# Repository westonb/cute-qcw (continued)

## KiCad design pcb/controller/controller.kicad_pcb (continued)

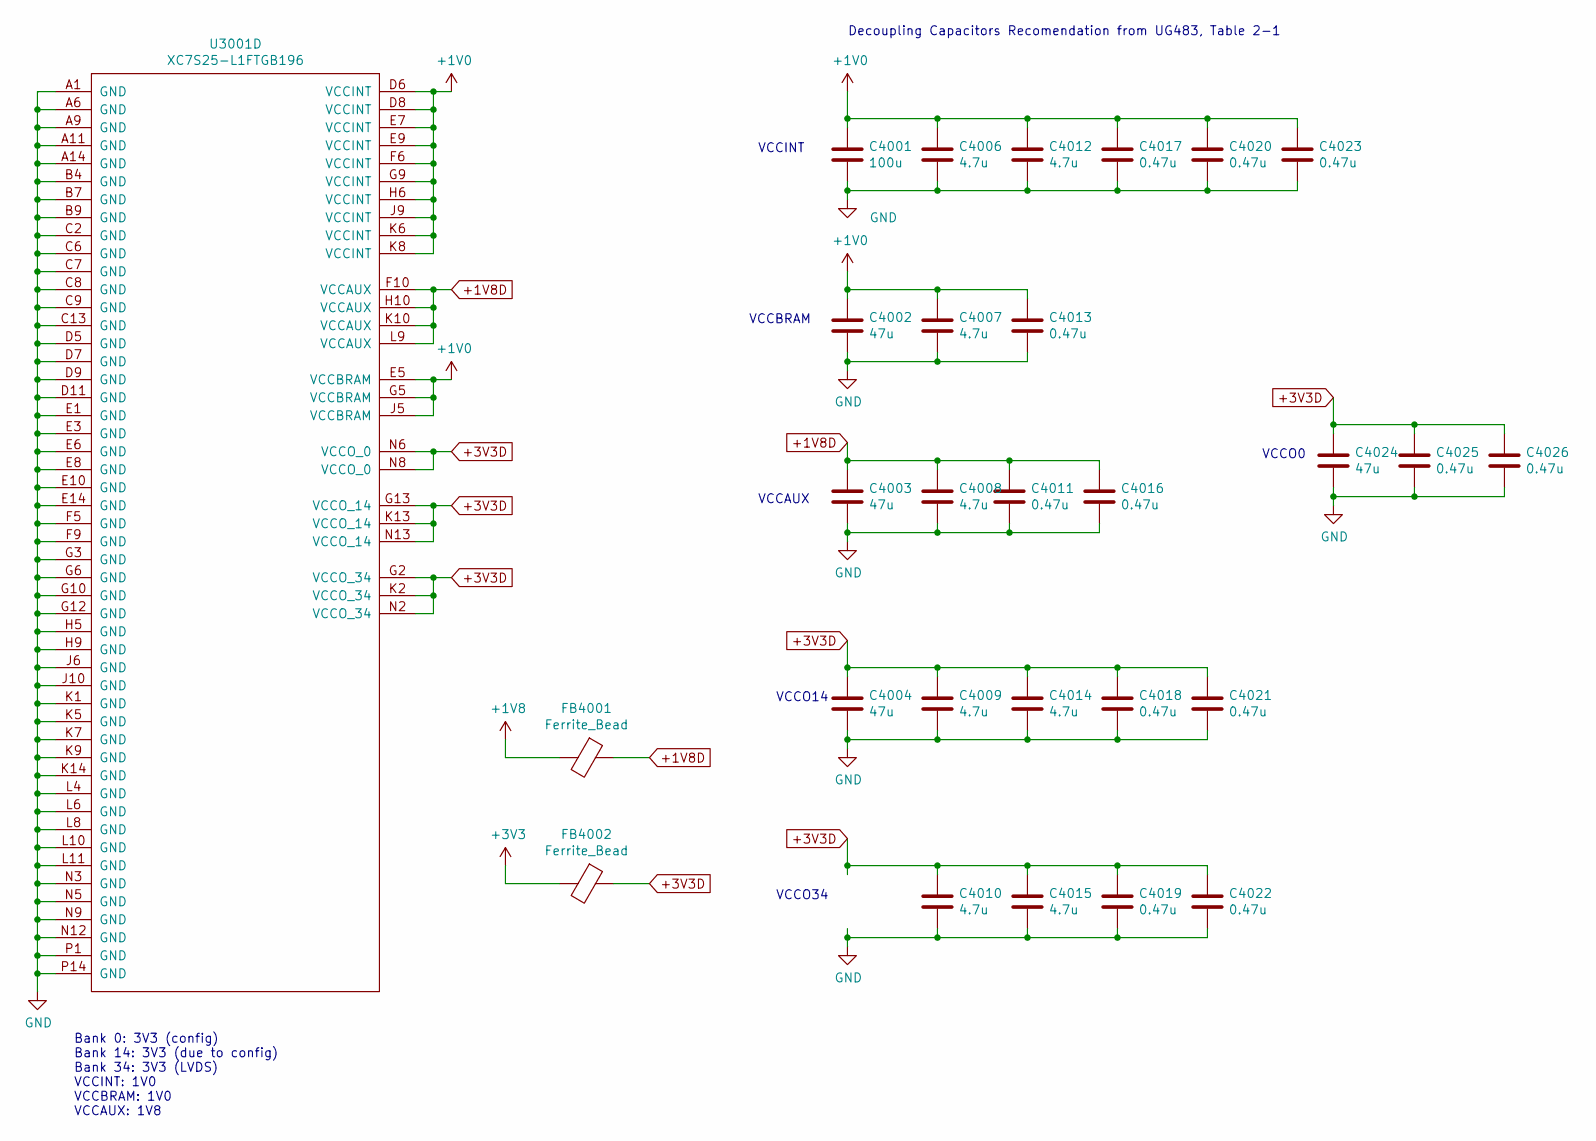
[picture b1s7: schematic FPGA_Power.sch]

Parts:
C4001: 100u; C_0805_2012Metric
C4002, C4003, C4004, C4024: 47u; C_0805_2012Metric
C4006, C4007, C4008, C4009, C4010, C4012, C4014, C4015: 4.7u; C_0402_1005Metric
C4011, C4013, C4016, C4017, C4018, C4019, C4020, C4021, C4022, C4023, C4025, C4026: 0.47u; C_0402_1005Metric
FB4001, FB4002: Ferrite_Bead; L_0805_2012Metric
U3001: XC7S25-L1FTGB196; FTGB196

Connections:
+1V0: C4001.1, C4002.1, C4006.1, C4007.1, C4012.1, C4013.1, C4017.1, C4020.1, C4023.1, U3001.D6 (VCCINT), U3001.D8 (VCCINT), U3001.E5 (VCCBRAM), U3001.E7 (VCCINT), U3001.E9 (VCCINT), U3001.F6 (VCCINT), U3001.G5 (VCCBRAM), U3001.G9 (VCCINT), U3001.H6 (VCCINT), U3001.J5 (VCCBRAM), U3001.J9 (VCCINT), U3001.K6 (VCCINT), U3001.K8 (VCCINT); also elsewhere on the board
+1V8: FB4001.2; also elsewhere on the board
+1V8D: C4003.1, C4008.1, C4011.1, C4016.1, FB4001.1, U3001.F10 (VCCAUX), U3001.H10 (VCCAUX), U3001.K10 (VCCAUX), U3001.L9 (VCCAUX); also elsewhere on the board
+3V3: FB4002.2; also elsewhere on the board
+3V3D: C4004.1, C4009.1, C4010.1, C4014.1, C4015.1, C4018.1, C4019.1, C4021.1, C4022.1, C4024.1, C4025.1, C4026.1, FB4002.1, U3001.G2 (VCCO_34), U3001.G13 (VCCO_14), U3001.K2 (VCCO_34), U3001.K13 (VCCO_14), U3001.N2 (VCCO_34), U3001.N6 (VCCO_0), U3001.N8 (VCCO_0), U3001.N13 (VCCO_14); also elsewhere on the board
GND: C4001.2, C4002.2, C4003.2, C4004.2, C4006.2, C4007.2, C4008.2, C4009.2, C4010.2, C4011.2, C4012.2, C4013.2, C4014.2, C4015.2, C4016.2, C4017.2, C4018.2, C4019.2, C4020.2, C4021.2, C4022.2, C4023.2, C4024.2, C4025.2, C4026.2, U3001.A1 (GND), U3001.A6 (GND), U3001.A9 (GND), U3001.A11 (GND), U3001.A14 (GND), U3001.B4 (GND), U3001.B7 (GND), U3001.B9 (GND), U3001.C2 (GND), U3001.C6 (GND), U3001.C7 (GND), U3001.C8 (GND), U3001.C9 (GND), U3001.C13 (GND), U3001.D5 (GND), U3001.D7 (GND), U3001.D9 (GND), U3001.D11 (GND), U3001.E1 (GND), U3001.E3 (GND), U3001.E6 (GND), U3001.E8 (GND), U3001.E10 (GND), U3001.E14 (GND), U3001.F5 (GND), U3001.F9 (GND), U3001.G3 (GND), U3001.G6 (GND), U3001.G10 (GND), U3001.G12 (GND), U3001.H5 (GND), U3001.H9 (GND), U3001.J6 (GND), U3001.J10 (GND), U3001.K1 (GND), U3001.K5 (GND), U3001.K7 (GND), U3001.K9 (GND), U3001.K14 (GND), U3001.L4 (GND), U3001.L6 (GND), U3001.L8 (GND), U3001.L10 (GND), U3001.L11 (GND), U3001.N3 (GND), U3001.N5 (GND), U3001.N9 (GND), U3001.N12 (GND), U3001.P1 (GND), U3001.P14 (GND); also elsewhere on the board

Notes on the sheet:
Decoupling Capacitors Recomendation from UG483, Table 2-1
VCCINT
VCCBRAM
VCCAUX
VCCO14
Bank 0: 3V3 (config) Bank 14: 3V3 (due to config) Bank 34: 3V3 (LVDS) VCCINT: 1V0 VCCBRAM: 1V0 VCCAUX: 1V8
VCCO34
VCCO0

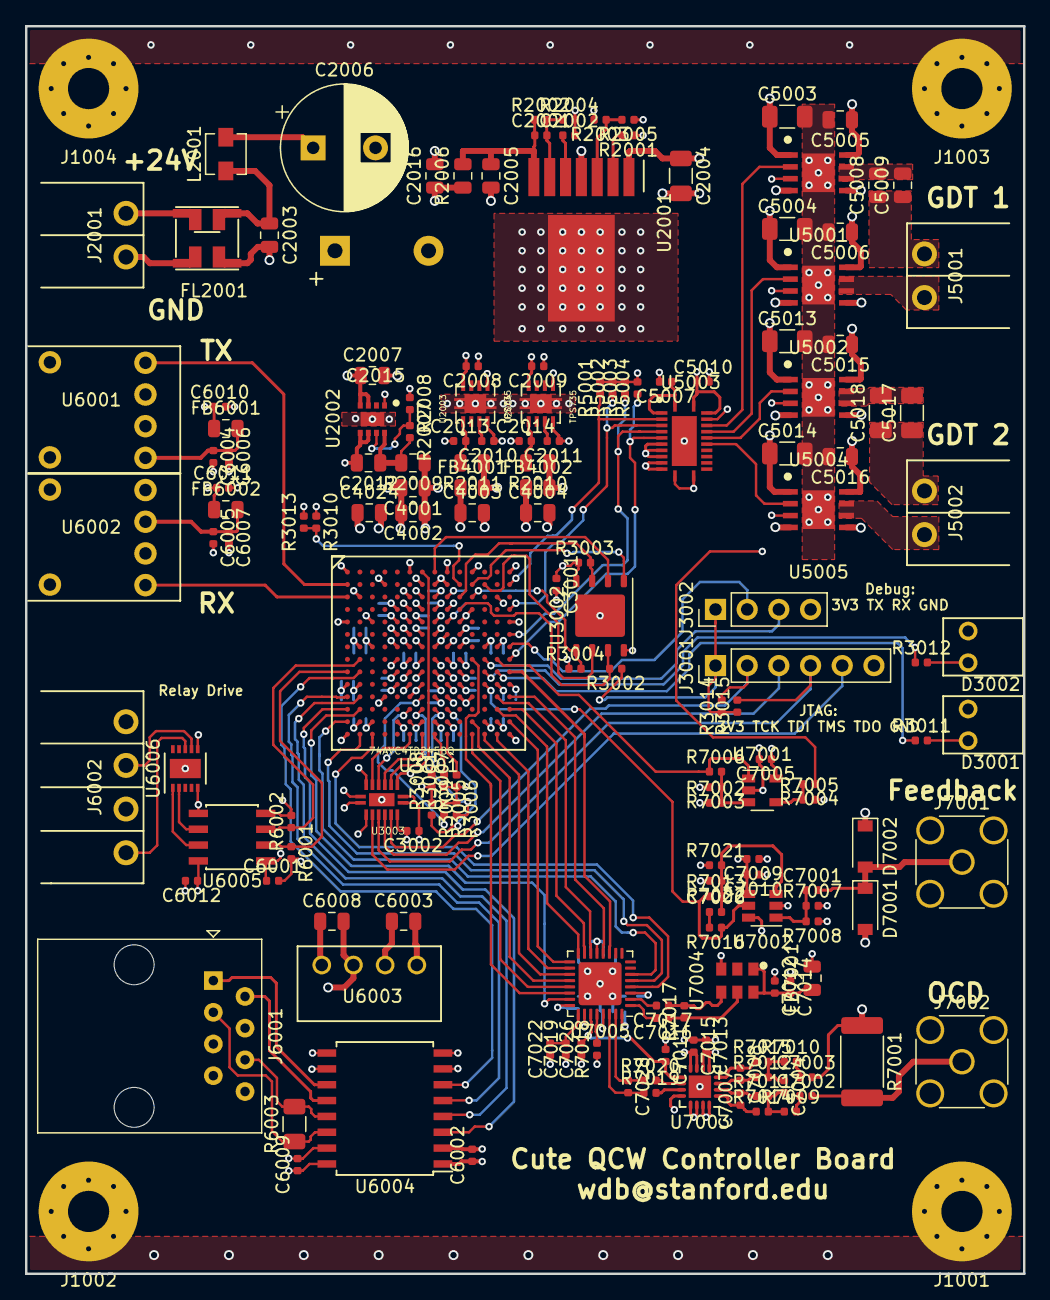
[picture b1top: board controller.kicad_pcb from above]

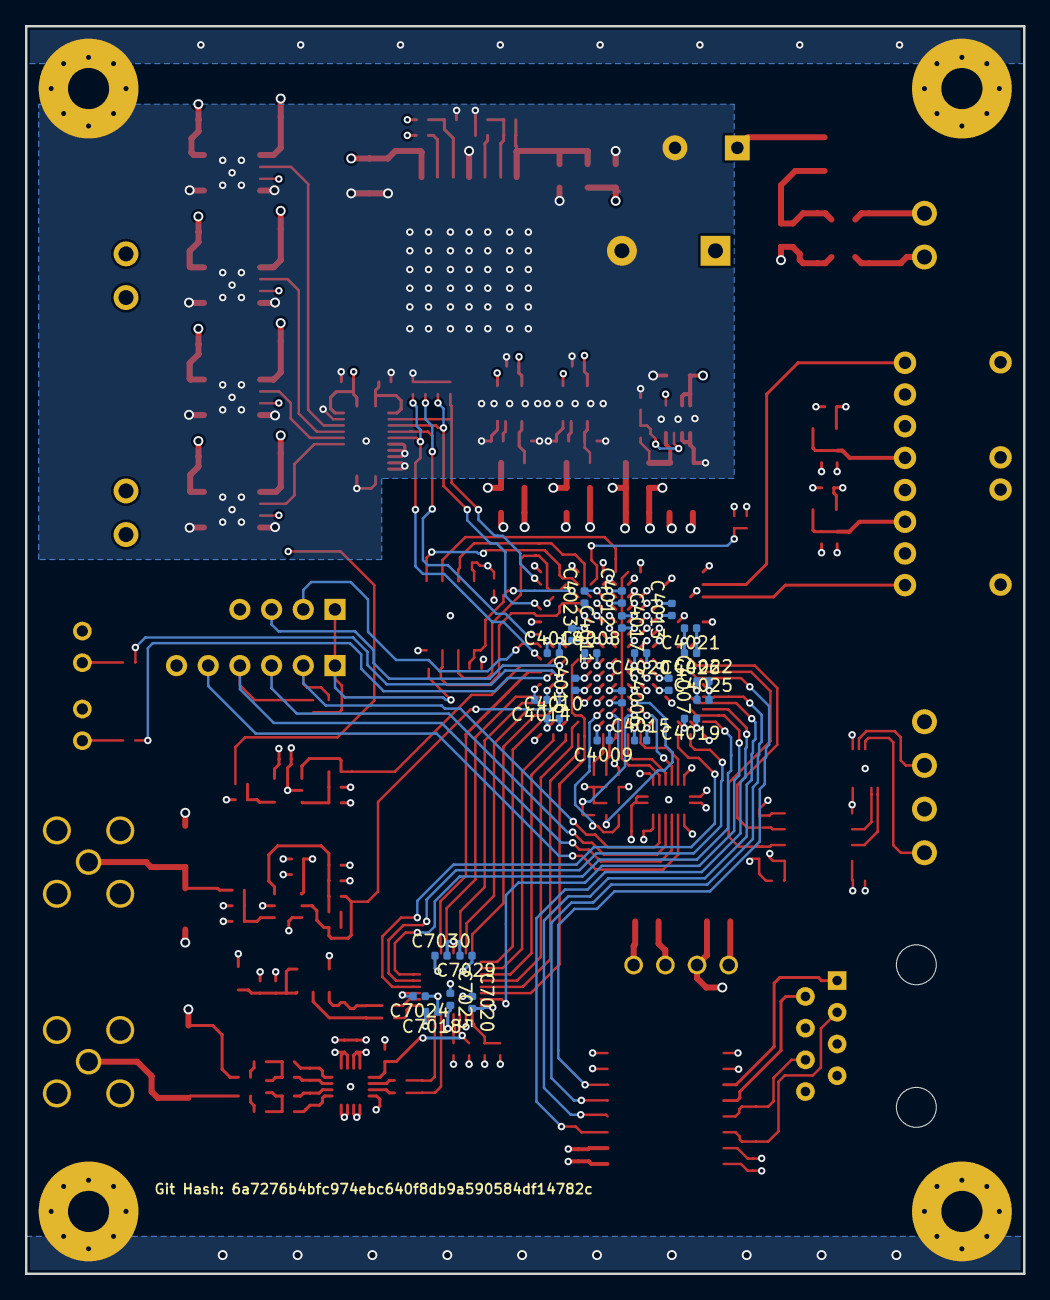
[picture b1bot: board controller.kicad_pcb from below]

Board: 4 copper layers, 80.0 x 100.0 mm, 198 parts (26 on the bottom side), 128 nets.

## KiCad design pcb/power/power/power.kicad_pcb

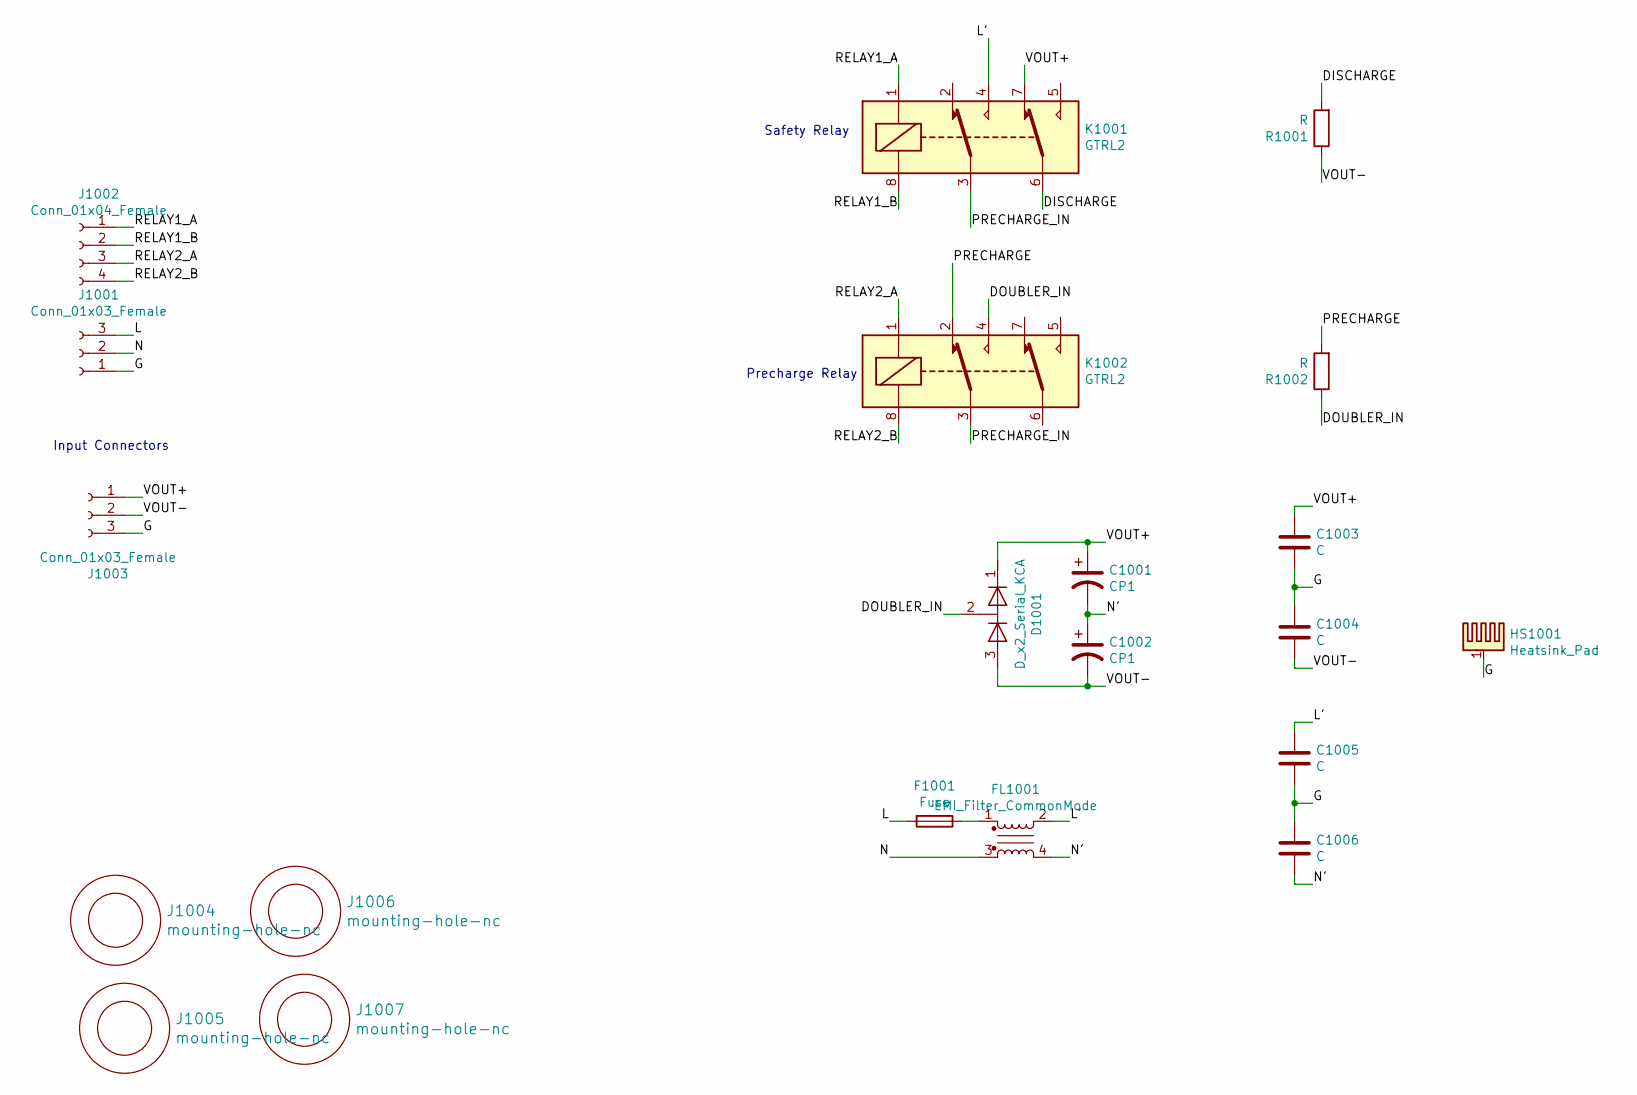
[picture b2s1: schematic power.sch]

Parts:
C1001, C1002: CP1; CP_Radial_D25.0mm_P10.00mm_SnapIn
C1003, C1004, C1005, C1006: C; C_Rect_L18.0mm_W8.0mm_P15.00mm_FKS3_FKP3
D1001: D_x2_Serial_KCA; TO-247-3_Vertical
F1001: Fuse; Fuseholder_Cylinder-5x20mm_Schurter_0031_8201_Horizontal_Op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
FL1001: EMI_Filter_CommonMode; 744824622
HS1001: Heatsink_Pad; RA-T2X
J1001, J1003: Conn_01x03_Female; Terminal-block-plug_3x1_5mm-pitch
J1002: Conn_01x04_Female; Terminal-block-plug_4x1_3.5mm-pitch
J1004, J1005, J1006, J1007: mounting-hole-nc; M3-mounting-hole-insulated
K1001, K1002: GTRL2; G2RL-2
R1001, R1002: R; RESISTOR_CW010

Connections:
/DISCHARGE: K1001.6, R1001.2
/DOUBLER_IN: D1001.2 (common), K1002.4, R1002.1
/G: C1003.2, C1004.1, C1005.2, C1006.1, HS1001.1, J1001.1, J1003.3
/L: F1001.2, J1001.3
/L': C1005.1, FL1001.2, K1001.4
/N: FL1001.3, J1001.2
/N': C1001.2, C1002.1, C1006.2, FL1001.4
/PRECHARGE: K1002.2, R1002.2
/PRECHARGE_IN: K1001.3, K1002.3
/RELAY1_A: J1002.1, K1001.1
/RELAY1_B: J1002.2, K1001.8
/RELAY2_A: J1002.3, K1002.1
/RELAY2_B: J1002.4, K1002.8
/VOUT+: C1001.1, C1003.1, D1001.1 (K), J1003.1, K1001.7
/VOUT-: C1002.2, C1004.2, D1001.3 (A), J1003.2, R1001.1
unnamed: F1001.1, FL1001.1

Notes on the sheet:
Safety Relay
Precharge Relay
Input Connectors

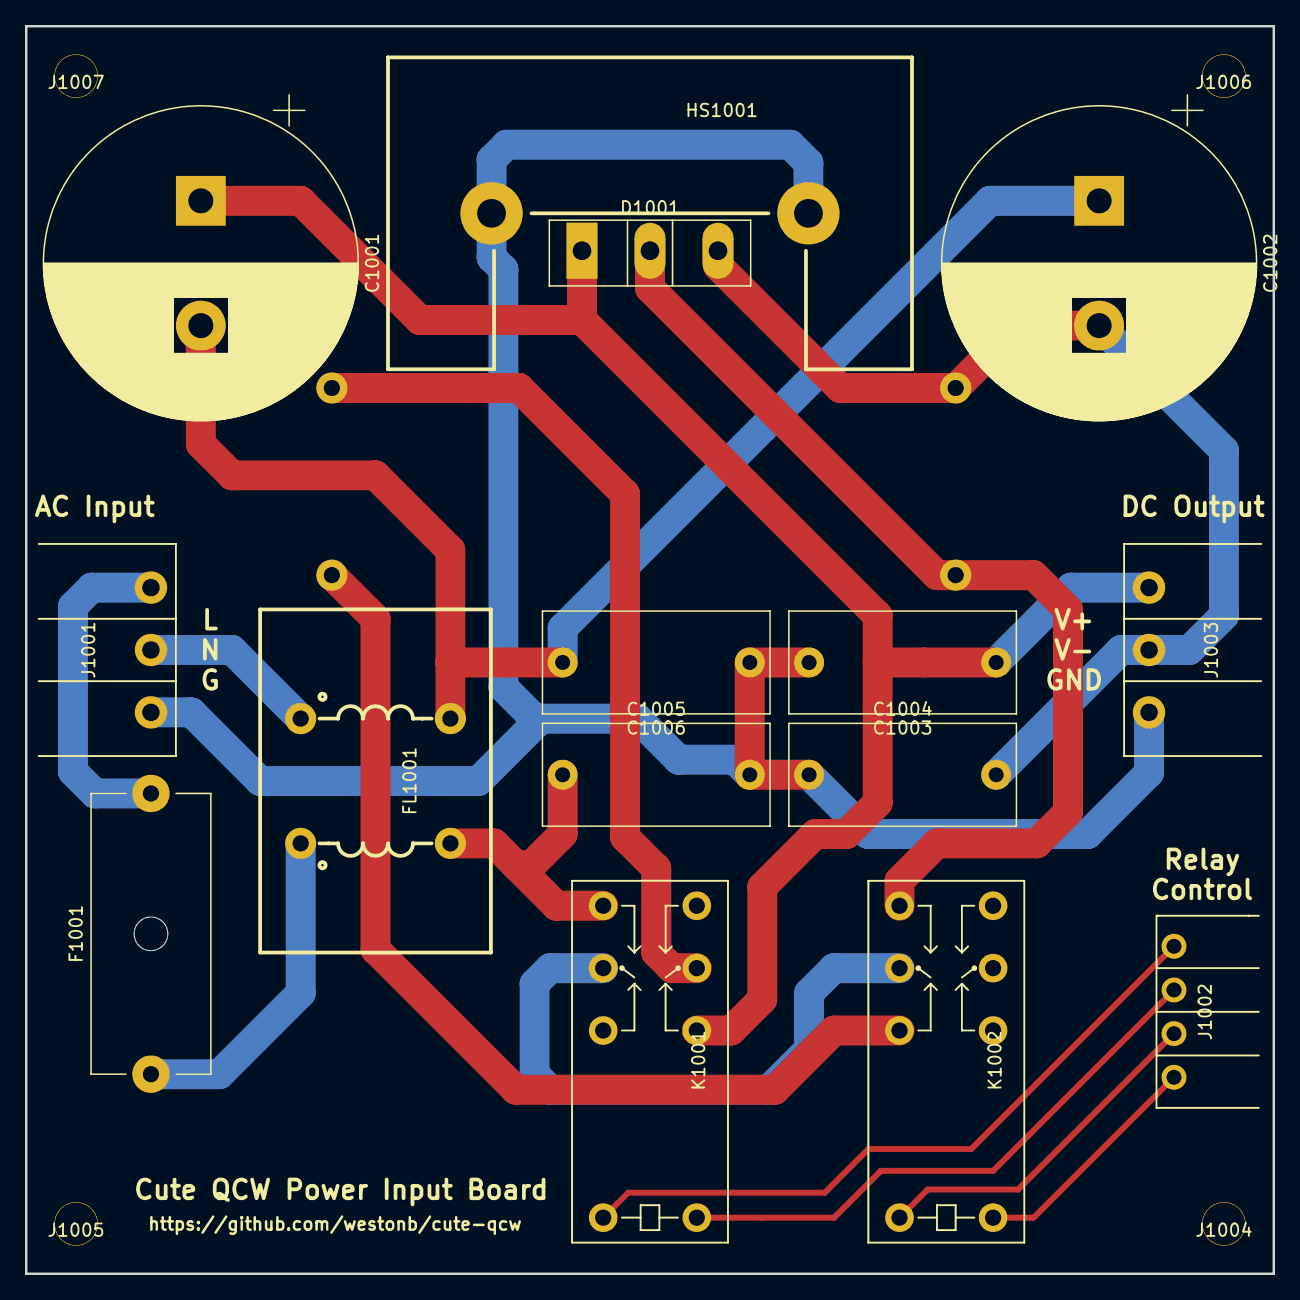
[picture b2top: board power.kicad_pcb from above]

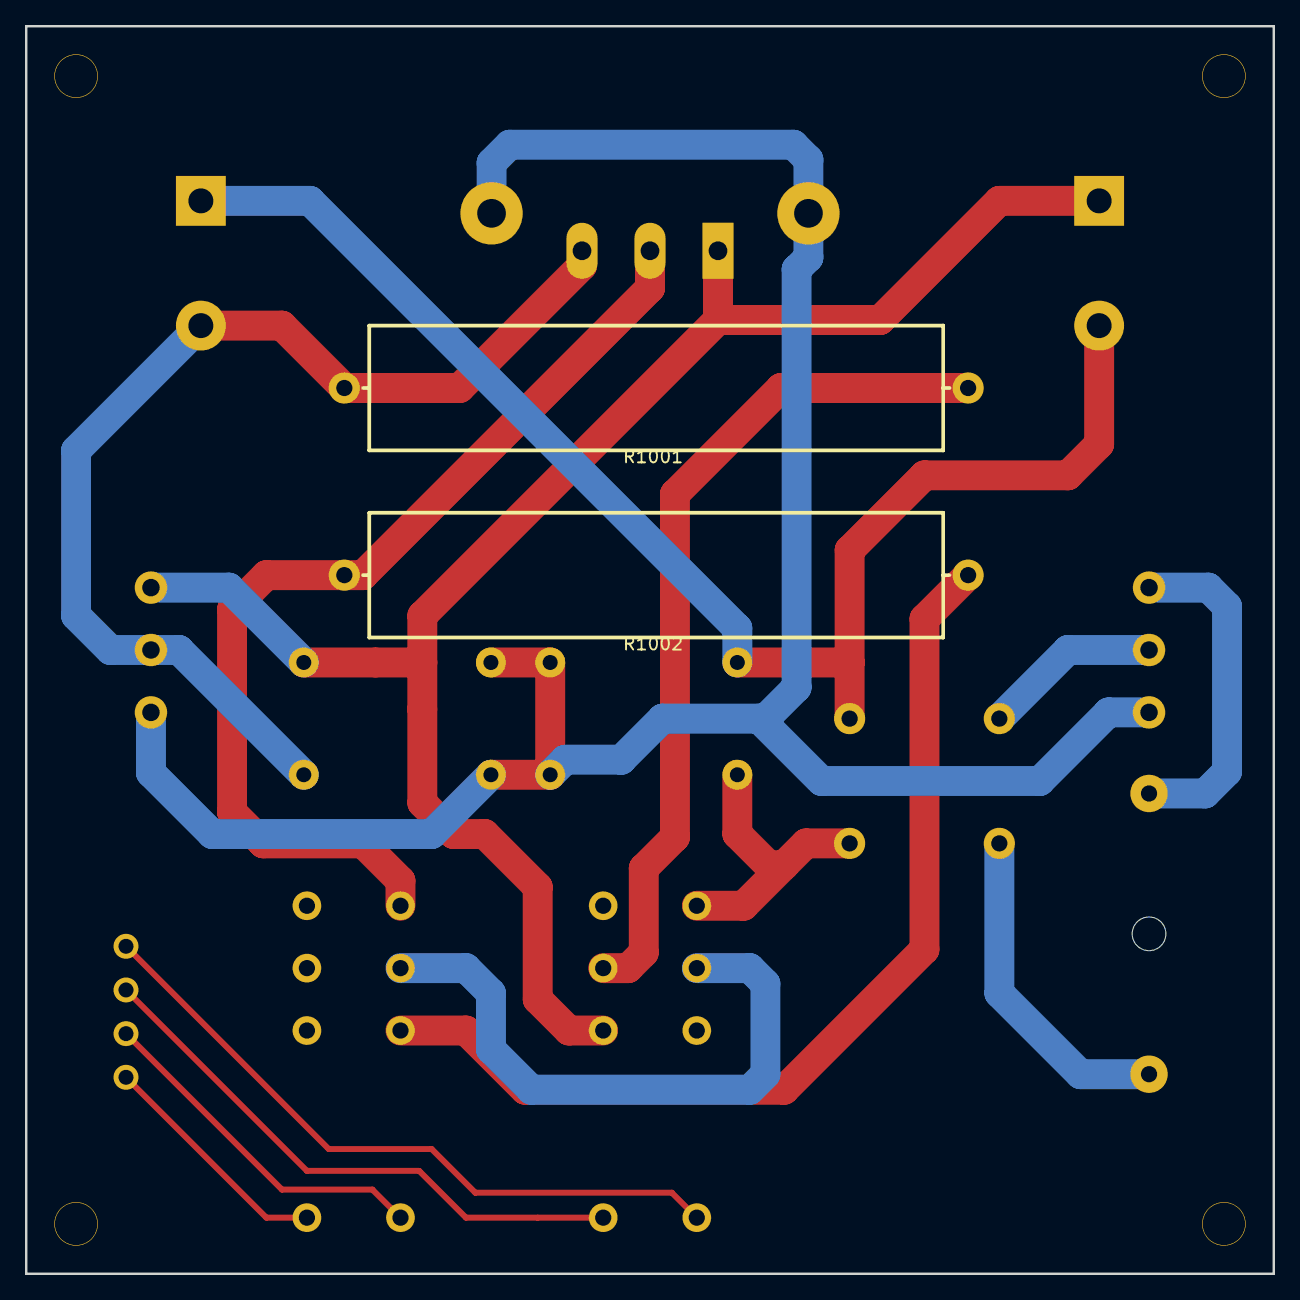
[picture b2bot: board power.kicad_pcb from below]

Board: 2 copper layers, 100.0 x 100.0 mm, 21 parts (2 on the bottom side), 16 nets.

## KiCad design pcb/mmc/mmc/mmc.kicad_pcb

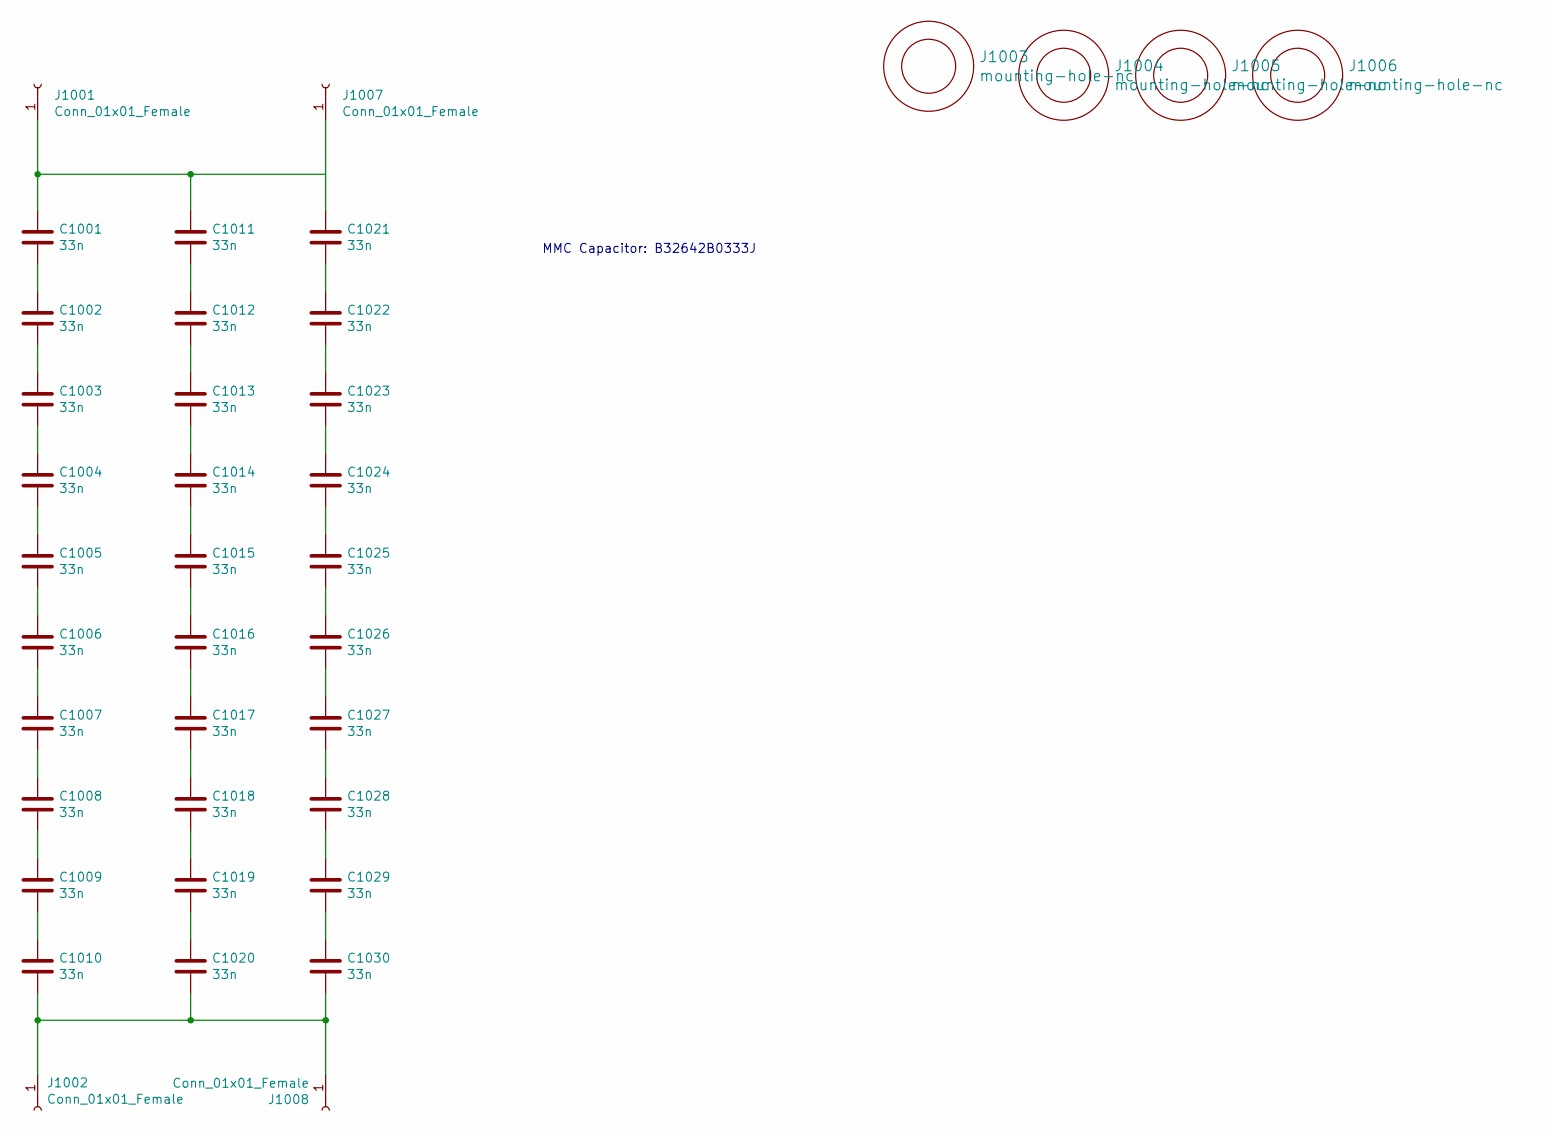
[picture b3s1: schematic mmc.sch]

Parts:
C1001, C1002, C1003, C1004, C1005, C1006, C1007, C1008, C1009, C1010, C1011, C1012, C1013, C1014, C1015, C1016, C1017, C1018, C1019, C1020, C1021, C1022, C1023, C1024, C1025, C1026, C1027, C1028, C1029, C1030: 33n; C_Rect_L18.0mm_W7.0mm_P15.00mm_FKS3_FKP3
J1001, J1002, J1007, J1008: Conn_01x01_Female; 7693-term
J1003, J1004, J1005, J1006: mounting-hole-nc; M3-mounting-hole-insulated

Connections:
unnamed: C1001.1, C1011.1, C1021.1, J1001.1, J1007.1
unnamed: C1001.2, C1002.1
unnamed: C1002.2, C1003.1
unnamed: C1003.2, C1004.1
unnamed: C1004.2, C1005.1
unnamed: C1005.2, C1006.1
unnamed: C1006.2, C1007.1
unnamed: C1007.2, C1008.1
unnamed: C1008.2, C1009.1
unnamed: C1009.2, C1010.1
unnamed: C1010.2, C1020.2, C1030.2, J1002.1, J1008.1
unnamed: C1011.2, C1012.1
unnamed: C1012.2, C1013.1
unnamed: C1013.2, C1014.1
unnamed: C1014.2, C1015.1
unnamed: C1015.2, C1016.1
unnamed: C1016.2, C1017.1
unnamed: C1017.2, C1018.1
unnamed: C1018.2, C1019.1
unnamed: C1019.2, C1020.1
unnamed: C1021.2, C1022.1
unnamed: C1022.2, C1023.1
unnamed: C1023.2, C1024.1
unnamed: C1024.2, C1025.1
unnamed: C1025.2, C1026.1
unnamed: C1026.2, C1027.1
unnamed: C1027.2, C1028.1
unnamed: C1028.2, C1029.1
unnamed: C1029.2, C1030.1

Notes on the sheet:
MMC Capacitor: B32642B0333J

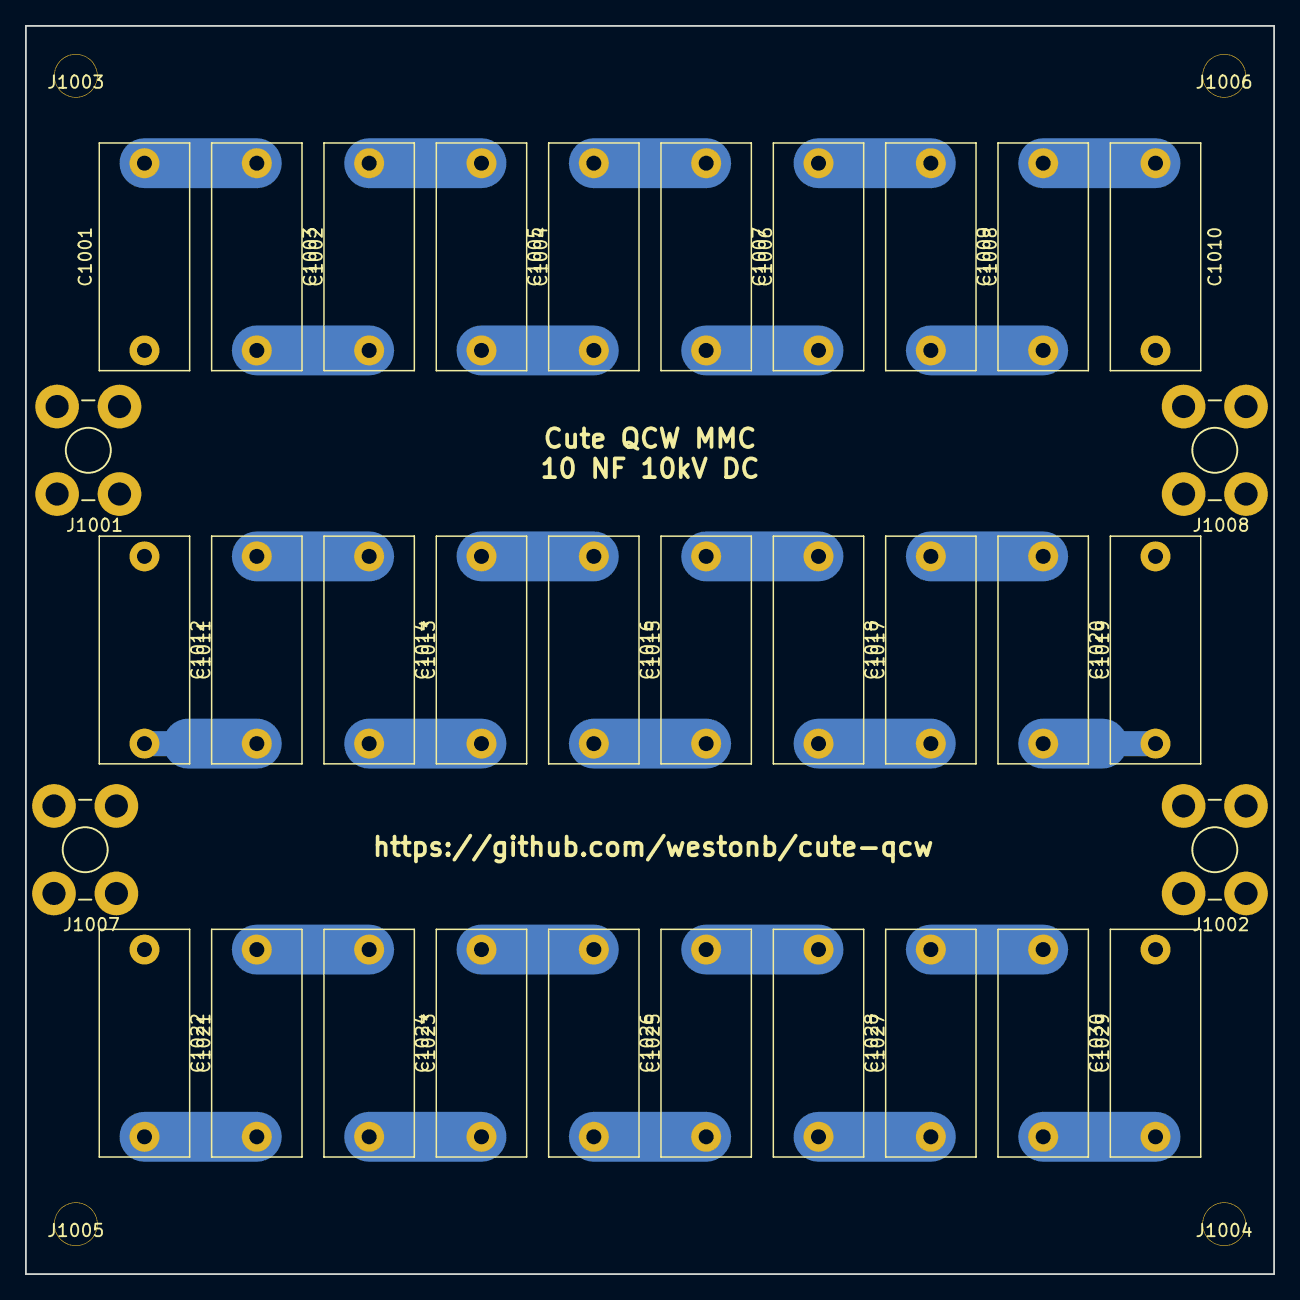
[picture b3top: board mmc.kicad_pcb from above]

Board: 2 copper layers, 100.0 x 100.0 mm, 38 parts (0 on the bottom side), 29 nets.

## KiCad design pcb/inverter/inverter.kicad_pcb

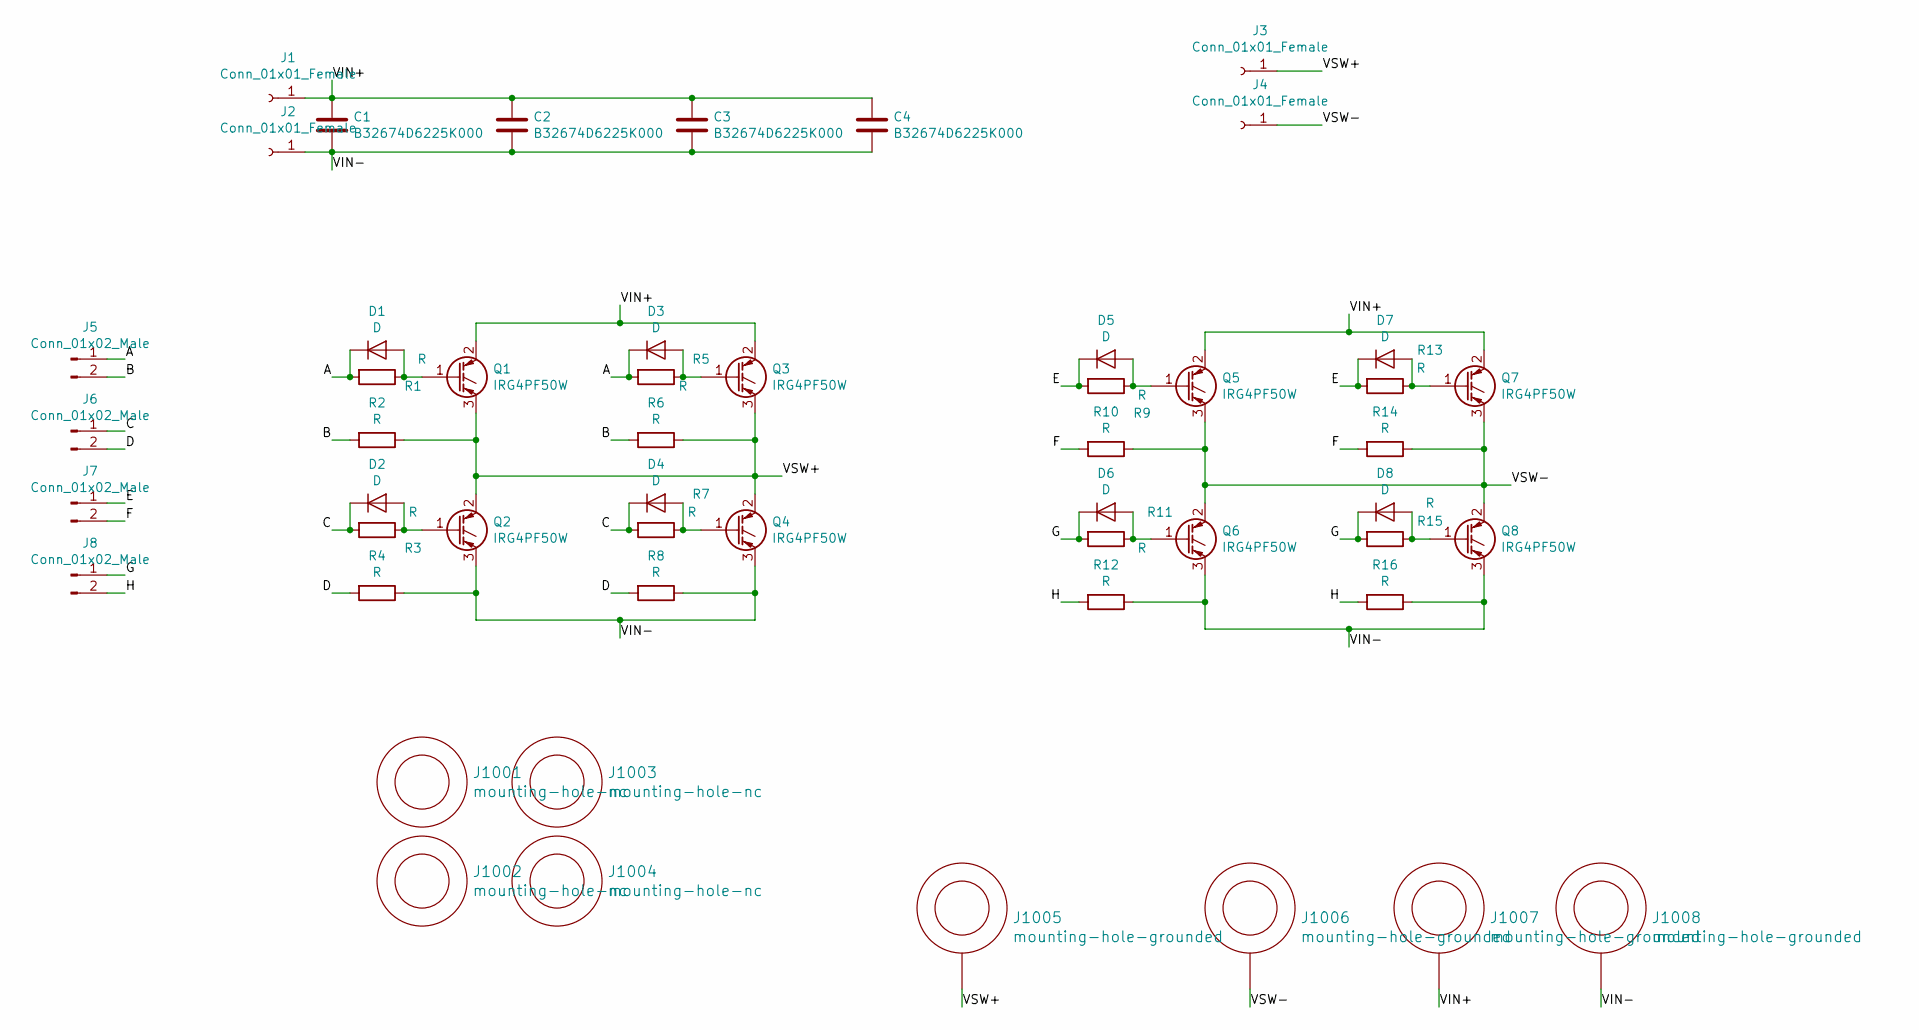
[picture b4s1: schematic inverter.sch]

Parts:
C1, C2, C3, C4: B32674D6225K000; C_Rect_L31.5mm_W17.0mm_P27.50mm_MKS4
D1, D2, D3, D4, D5, D6, D7, D8: D; D_SOD-123F
J1, J2, J3, J4: Conn_01x01_Female; 7693-term
J5, J6, J7, J8: Conn_01x02_Male; PinHeader_1x02_P2.54mm_Vertical
J1001, J1002, J1003, J1004: mounting-hole-nc; M3-through-hole
J1005, J1006, J1007, J1008: mounting-hole-grounded; M3-tight-fit-pan-head
Q1, Q2, Q3, Q4, Q5, Q6, Q7, Q8: IRG4PF50W; TO-247-3_Vertical
R1, R2, R3, R4, R5, R6, R7, R8, R9, R10, R11, R12, R13, R14, R15, R16: R; R_1206_3216Metric

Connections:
/A: D1.1 (K), D3.1 (K), J5.1, R1.2, R5.2
/B: J5.2, R2.2, R6.2
/C: D2.1 (K), D4.1 (K), J6.1, R3.2, R7.2
/D: J6.2, R4.2, R8.2
/E: D5.1 (K), D7.1 (K), J7.1, R9.2, R13.2
/F: J7.2, R10.2, R14.2
/G: D6.1 (K), D8.1 (K), J8.1, R11.2, R15.2
/H: J8.2, R12.2, R16.2
/VIN+: C1.1, C2.1, C3.1, C4.1, J1.1, J1007.1, Q1.2 (C), Q3.2 (C), Q5.2 (C), Q7.2 (C)
/VIN-: C1.2, C2.2, C3.2, C4.2, J2.1, J1008.1, Q2.3 (E), Q4.3 (E), Q6.3 (E), Q8.3 (E), R4.1, R8.1, R12.1, R16.1
/VSW+: J3.1, J1005.1, Q1.3 (E), Q2.2 (C), Q3.3 (E), Q4.2 (C), R2.1, R6.1
/VSW-: J4.1, J1006.1, Q5.3 (E), Q6.2 (C), Q7.3 (E), Q8.2 (C), R10.1, R14.1
unnamed: D1.2 (A), Q1.1 (G), R1.1
unnamed: D2.2 (A), Q2.1 (G), R3.1
unnamed: D3.2 (A), Q3.1 (G), R5.1
unnamed: D4.2 (A), Q4.1 (G), R7.1
unnamed: D5.2 (A), Q5.1 (G), R9.1
unnamed: D6.2 (A), Q6.1 (G), R11.1
unnamed: D7.2 (A), Q7.1 (G), R13.1
unnamed: D8.2 (A), Q8.1 (G), R15.1

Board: 2 copper layers, 52 parts (0 on the bottom side), 20 nets, no tracks yet.

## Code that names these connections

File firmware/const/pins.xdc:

set_property CFGBVS VCCO [current_design]
set_property CONFIG_VOLTAGE 3.3 [current_design]

#ADC data bus
set_property PACKAGE_PIN J14 [get_ports ADC_DATA[0]]
set_property IOSTANDARD LVCMOS33 [get_ports ADC_DATA[0]]
set_property PACKAGE_PIN L14 [get_ports ADC_DATA[1]]
set_property IOSTANDARD LVCMOS33 [get_ports ADC_DATA[1]]
set_property PACKAGE_PIN L13 [get_ports ADC_DATA[2]]
set_property IOSTANDARD LVCMOS33 [get_ports ADC_DATA[2]]
set_property PACKAGE_PIN M14 [get_ports ADC_DATA[3]]
set_property IOSTANDARD LVCMOS33 [get_ports ADC_DATA[3]]
set_property PACKAGE_PIN M13 [get_ports ADC_DATA[4]]
set_property IOSTANDARD LVCMOS33 [get_ports ADC_DATA[4]]
set_property PACKAGE_PIN N14 [get_ports ADC_DATA[5]]
set_property IOSTANDARD LVCMOS33 [get_ports ADC_DATA[5]]
set_property PACKAGE_PIN P13 [get_ports ADC_DATA[6]]
set_property IOSTANDARD LVCMOS33 [get_ports ADC_DATA[6]]
set_property PACKAGE_PIN P12 [get_ports ADC_DATA[7]]
set_property IOSTANDARD LVCMOS33 [get_ports ADC_DATA[7]]
set_property PACKAGE_PIN N11 [get_ports ADC_DATA[8]]
set_property IOSTANDARD LVCMOS33 [get_ports ADC_DATA[8]]
set_property PACKAGE_PIN P11 [get_ports ADC_DATA[9]]
set_property IOSTANDARD LVCMOS33 [get_ports ADC_DATA[9]]

#ADC other signals
set_property PACKAGE_PIN H11 [get_ports ADC_DCO]
set_property IOSTANDARD LVCMOS33 [get_ports ADC_DCO]
set_property PACKAGE_PIN M2 [get_ports ADC_MODE]
set_property IOSTANDARD LVCMOS33 [get_ports ADC_MODE]
set_property PACKAGE_PIN P2 [get_ports ADC_SCLK]
set_property IOSTANDARD LVCMOS33 [get_ports ADC_SCLK]
set_property PACKAGE_PIN N1 [get_ports ADC_SDIO]
set_property IOSTANDARD LVCMOS33 [get_ports ADC_SDIO]
set_property PACKAGE_PIN P3 [get_ports ADC_CS]
set_property IOSTANDARD LVCMOS33 [get_ports ADC_CS]

#debug / status 
set_property PACKAGE_PIN J13 [get_ports LED1]
set_property IOSTANDARD LVCMOS33 [get_ports LED1]
set_property PACKAGE_PIN J12 [get_ports LED2]
set_property IOSTANDARD LVCMOS33 [get_ports LED2]
set_property PACKAGE_PIN G14 [get_ports DEBUG_TX]
set_property IOSTANDARD LVCMOS33 [get_ports DEBUG_TX]
set_property PACKAGE_PIN H12 [get_ports DEBUG_RX]
set_property IOSTANDARD LVCMOS33 [get_ports DEBUG_RX]

#interface
set_property PACKAGE_PIN B1 [get_ports FIBER_TX]
set_property IOSTANDARD LVCMOS33 [get_ports FIBER_TX]
set_property PACKAGE_PIN C1 [get_ports FIBER_RX]
set_property IOSTANDARD LVCMOS33 [get_ports FIBER_RX]
set_property PACKAGE_PIN J2 [get_ports RS485D]
set_property IOSTANDARD LVCMOS33 [get_ports RS485D]
set_property PACKAGE_PIN L1 [get_ports RS485DE]
set_property IOSTANDARD LVCMOS33 [get_ports RS485DE]
set_property PACKAGE_PIN M1 [get_ports RS485R]
set_property IOSTANDARD LVCMOS33 [get_ports RS485R]
set_property PACKAGE_PIN L2 [get_ports RS485RE]
set_property IOSTANDARD LVCMOS33 [get_ports RS485RE]
set_property PACKAGE_PIN J1 [get_ports RELAY1]
set_property IOSTANDARD LVCMOS33 [get_ports RELAY1]
set_property PACKAGE_PIN H2 [get_ports RELAY2]
set_property IOSTANDARD LVCMOS33 [get_ports RELAY2]

#comparators 
set_property PACKAGE_PIN H13 [get_ports ULVO]
set_property IOSTANDARD LVCMOS33 [get_ports ULVO]
set_property PACKAGE_PIN K12 [get_ports ZCS]
set_property IOSTANDARD LVCMOS33 [get_ports ZCS]


#gate drive
set_property PACKAGE_PIN B14 [get_ports GATE1_P]
set_property IOSTANDARD LVCMOS33 [get_ports GATE1_P]
set_property PACKAGE_PIN D14 [get_ports GATE1_N]
set_property IOSTANDARD LVCMOS33 [get_ports GATE1_N]
set_property PACKAGE_PIN F14 [get_ports GATE2_P]
set_property IOSTANDARD LVCMOS33 [get_ports GATE2_P]
set_property PACKAGE_PIN H14 [get_ports GATE2_N]
set_property IOSTANDARD LVCMOS33 [get_ports GATE2_N]

#enable pullup on debug RX
set_property PULLUP TRUE [get_ports DEBUG_RX]

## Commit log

2018-02-02 first schematic revision mostly done
2018-10-26 finished inverter PCB layout
2019-01-17 started FPGA based controller design
2019-01-18 controller schematic capture almost done
2019-01-19 started assigning footprints
2019-01-20 pcb component placement almost done
2019-01-21 controller PCB routing progress
2019-01-21 routing almost done
2019-01-22 controller layout done and schematic reviewed
2019-01-22 generated gerbers
2019-01-22 inverter PCB layout finished
2019-01-23 created inverter gerbers
2019-01-23 created schematic for power input board
2019-01-23 started MMC PCB
2019-01-23 regenerated all gerbers and ordered controller and inverter pcbs
2019-01-24 updated controller schematic
2019-01-25 finished power and MMC PCBs and created gerbers
2019-01-25 generated PDF schematics of all PCBs
2019-02-12 updated schematic component values
2019-02-12 added stencil files
2019-02-28 added simulation files
2019-03-10 added verilog files for controller
2019-03-11 added verilog - analog cosimulation
2019-03-13 added PLL modules to top level verilog file
2019-03-14 first sparks
2019-03-14 started work on serdes based osc to improve resolution
2019-03-15 added serdes derived PLL
2019-03-15 first decent working firmware
